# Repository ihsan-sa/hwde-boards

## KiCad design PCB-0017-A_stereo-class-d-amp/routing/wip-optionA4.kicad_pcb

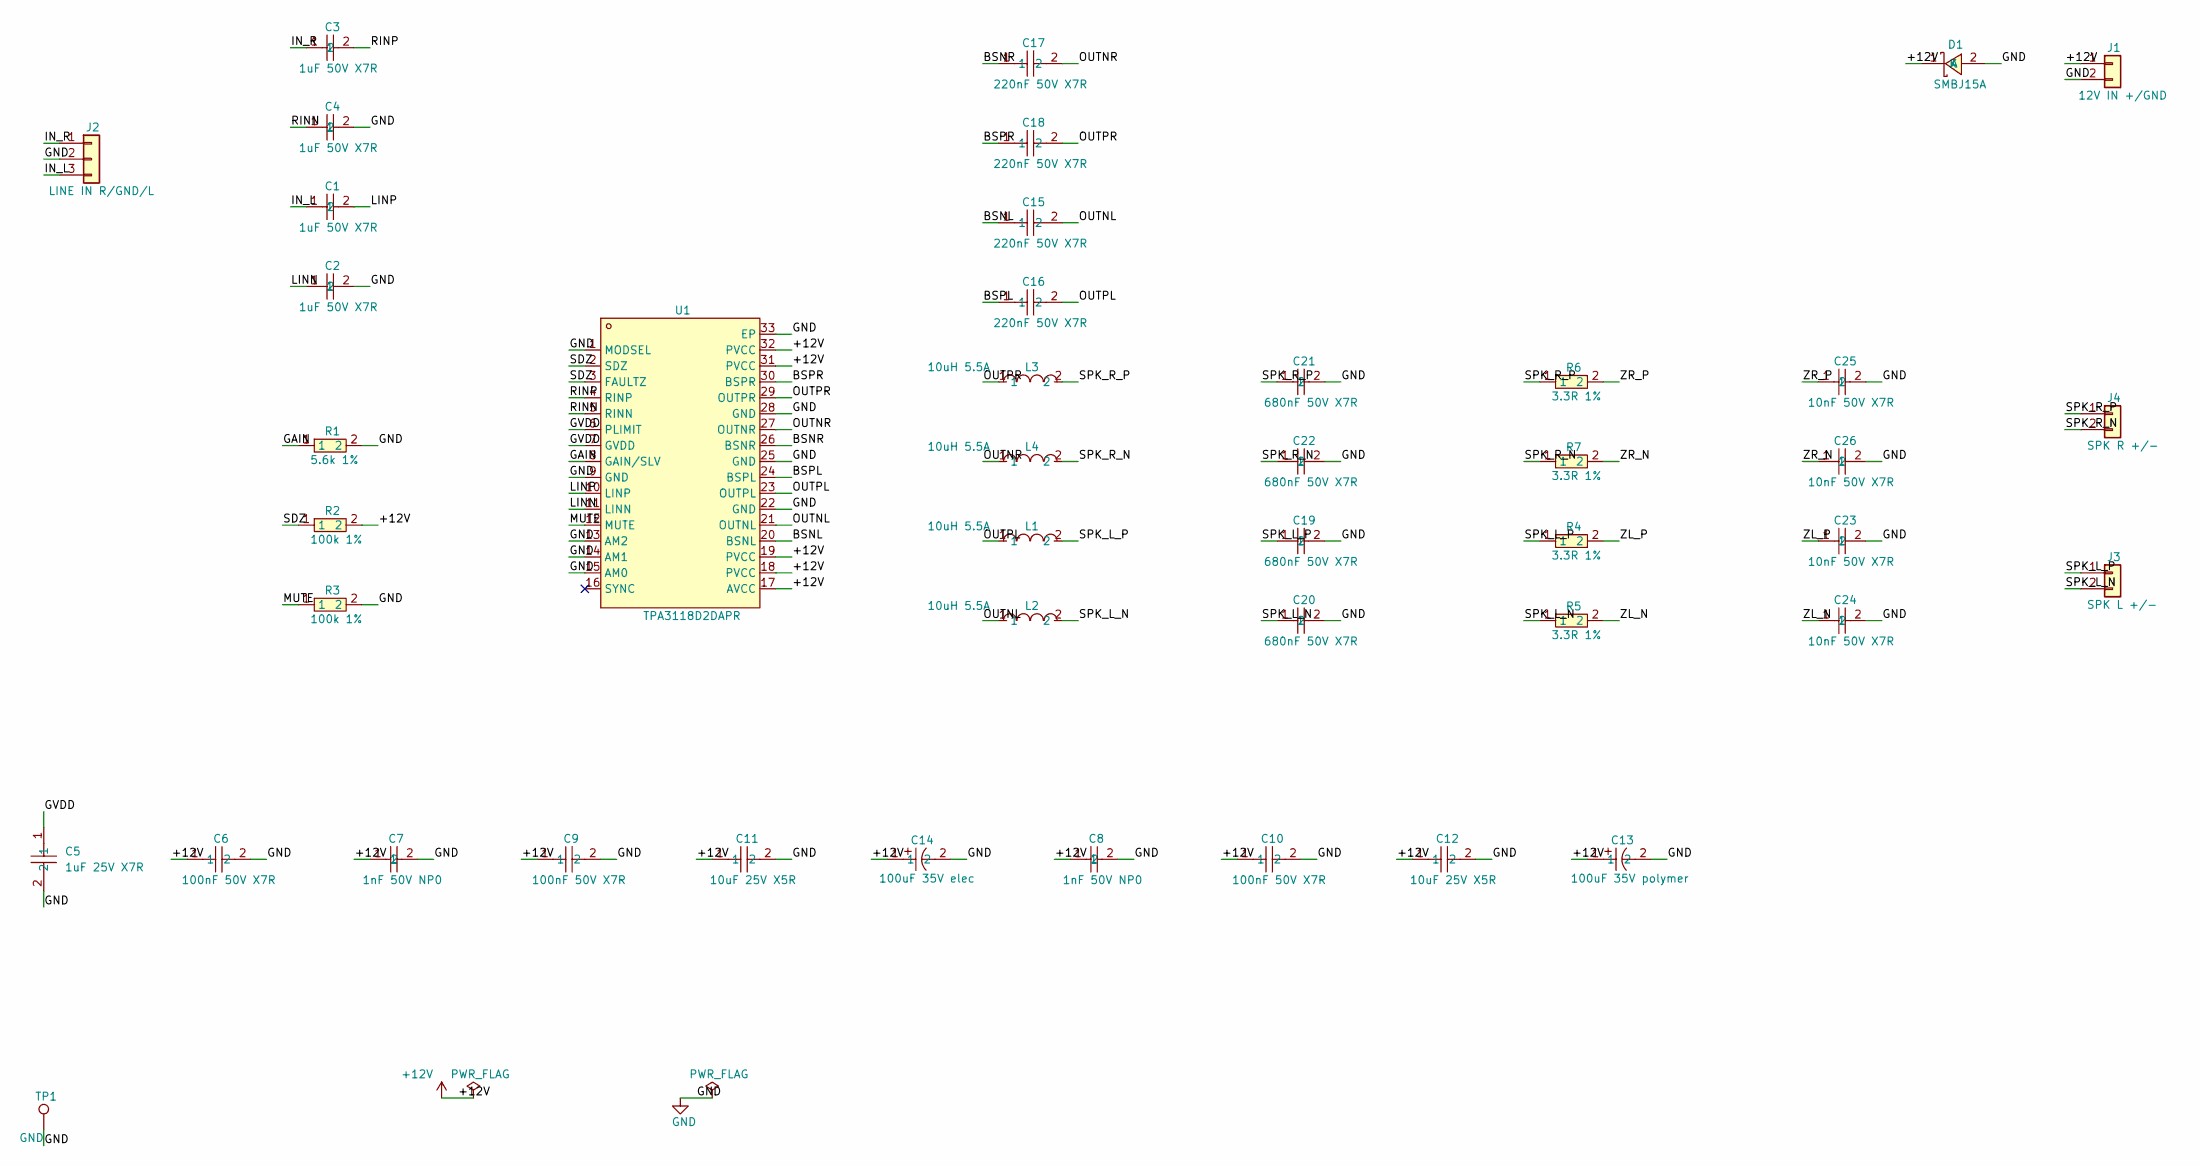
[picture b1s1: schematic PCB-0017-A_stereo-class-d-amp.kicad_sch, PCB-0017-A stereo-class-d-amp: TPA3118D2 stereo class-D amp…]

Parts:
C1, C2, C3, C4: 1uF 50V X7R; C0805; LCSC C28323
C5: 1uF 25V X7R; C0603; LCSC C106858
C6, C9, C10: 100nF 50V X7R; C0603; LCSC C14663
C7, C8: 1nF 50V NP0; C0603; LCSC C106246
C11, C12: 10uF 25V X5R; C0805; LCSC C15850
C13: 100uF 35V polymer; CAP-SMD_BD6.3-L6.6-W6.6-RD; LCSC C46550467
C14: 100uF 35V elec; CAP-SMD_BD6.3-L6.6-W6.6-LS7.3-FD; LCSC C2992596
C15, C16, C17, C18: 220nF 50V X7R; C0805; LCSC C5378
C19, C20, C21, C22: 680nF 50V X7R; C0805; LCSC C107133
C23, C24, C25, C26: 10nF 50V X7R; C0402; LCSC C15195
D1: SMBJ15A; SMB_L4.6-W3.6-LS5.3-RD; LCSC C113988
J1: 12V IN +/GND; WirePad_2P_3.0x6.0mm_P4.6mm
J2: LINE IN R/GND/L; WirePad_3P_1.5x3.0mm_P2.7mm
J3: SPK L +/-; WirePad_2P_3.0x6.0mm_P4.6mm
J4: SPK R +/-; WirePad_2P_3.0x6.0mm_P4.6mm
L1, L2, L3, L4: 10uH 5.5A; IND-SMD_L7.3-W6.6_MHCI06030; LCSC C207842
R1: 5.6k 1%; R0603; LCSC C23189
R2, R3: 100k 1%; R0603; LCSC C25803
R4, R5, R6, R7: 3.3R 1%; R0603; LCSC C137725
TP1: GND; TestPoint_SMD_1.5mm_Round
U1: TPA3118D2DAPR; HTSSOP-32_L11.0-W6.1-P0.65-LS8.1-BL-EP; LCSC C46497

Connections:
+12V: C6.1, C7.1, C8.1, C9.1, C10.1, C11.1, C12.1, C13.1, C14.1, D1.1 (K), J1.1, R2.2, U1.17 (AVCC), U1.18 (PVCC), U1.19 (PVCC), U1.31 (PVCC), U1.32 (PVCC)
/BSNL: C15.1, U1.20 (BSNL)
/BSNR: C17.1, U1.26 (BSNR)
/BSPL: C16.1, U1.24 (BSPL)
/BSPR: C18.1, U1.30 (BSPR)
/GAIN: R1.1, U1.8 (GAIN/SLV)
/GVDD: C5.1, U1.6 (PLIMIT), U1.7 (GVDD)
/IN_L: C1.1, J2.3
/IN_R: C3.1, J2.1
/LINN: C2.1, U1.11 (LINN)
/LINP: C1.2, U1.10 (LINP)
/MUTE: R3.1, U1.12 (MUTE)
/OUTNL: C15.2, L2.1, U1.21 (OUTNL)
/OUTNR: C17.2, L4.1, U1.27 (OUTNR)
/OUTPL: C16.2, L1.1, U1.23 (OUTPL)
/OUTPR: C18.2, L3.1, U1.29 (OUTPR)
/RINN: C4.1, U1.5 (RINN)
/RINP: C3.2, U1.4 (RINP)
/SDZ: R2.1, U1.2 (SDZ), U1.3 (FAULTZ)
/SPK_L_N: C20.1, J3.2, L2.2, R5.1
/SPK_L_P: C19.1, J3.1, L1.2, R4.1
/SPK_R_N: C22.1, J4.2, L4.2, R7.1
/SPK_R_P: C21.1, J4.1, L3.2, R6.1
/ZL_N: C24.1, R5.2
/ZL_P: C23.1, R4.2
/ZR_N: C26.1, R7.2
/ZR_P: C25.1, R6.2
GND: C2.2, C4.2, C5.2, C6.2, C7.2, C8.2, C9.2, C10.2, C11.2, C12.2, C13.2, C14.2, C19.2, C20.2, C21.2, C22.2, C23.2, C24.2, C25.2, C26.2, D1.2 (A), J1.2, J2.2, R1.2, R3.2, TP1.1, U1.1 (MODSEL), U1.9 (GND), U1.13 (AM2), U1.14 (AM1), U1.15 (AM0), U1.22 (GND), U1.25 (GND), U1.28 (GND), U1.33 (EP)

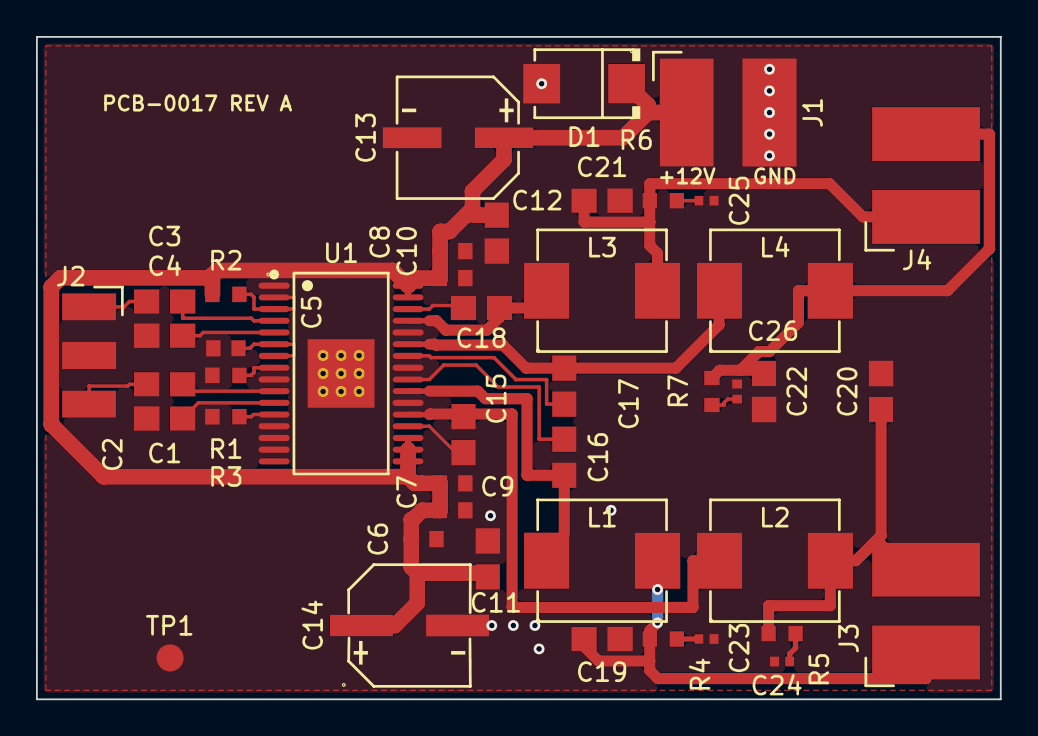
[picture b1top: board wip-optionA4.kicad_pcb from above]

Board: 2 copper layers, 53.5 x 36.8 mm, 44 parts (0 on the bottom side), 28 nets.

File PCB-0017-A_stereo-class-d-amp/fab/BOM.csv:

Comment,Designator,Footprint,LCSC Part #
1uF 50V X7R,"C1,C2,C3,C4",C0805,C28323
1uF 25V X7R,C5,C0603,C106858
100nF 50V X7R,"C6,C9,C10",C0603,C14663
1nF 50V NP0,"C7,C8",C0603,C106246
10uF 25V X5R,"C11,C12",C0805,C15850
100uF 35V polymer,C13,CAP-SMD_BD6.3-L6.6-W6.6-RD,C46550467
100uF 35V elec,C14,CAP-SMD_BD6.3-L6.6-W6.6-LS7.3-FD,C2992596
220nF 50V X7R,"C15,C16,C17,C18",C0805,C5378
680nF 50V X7R,"C19,C20,C21,C22",C0805,C107133
10nF 50V X7R,"C23,C24,C25,C26",C0402,C15195
SMBJ15A,D1,SMB_L4.6-W3.6-LS5.3-RD,C113988
10uH 5.5A,"L1,L2,L3,L4",IND-SMD_L7.3-W6.6_MHCI06030,C207842
5.6k 1%,R1,R0603,C23189
100k 1%,"R2,R3",R0603,C25803
3.3R 1%,"R4,R5,R6,R7",R0603,C137725
TPA3118D2DAPR,U1,HTSSOP-32_L11.0-W6.1-P0.65-LS8.1-BL-EP,C46497

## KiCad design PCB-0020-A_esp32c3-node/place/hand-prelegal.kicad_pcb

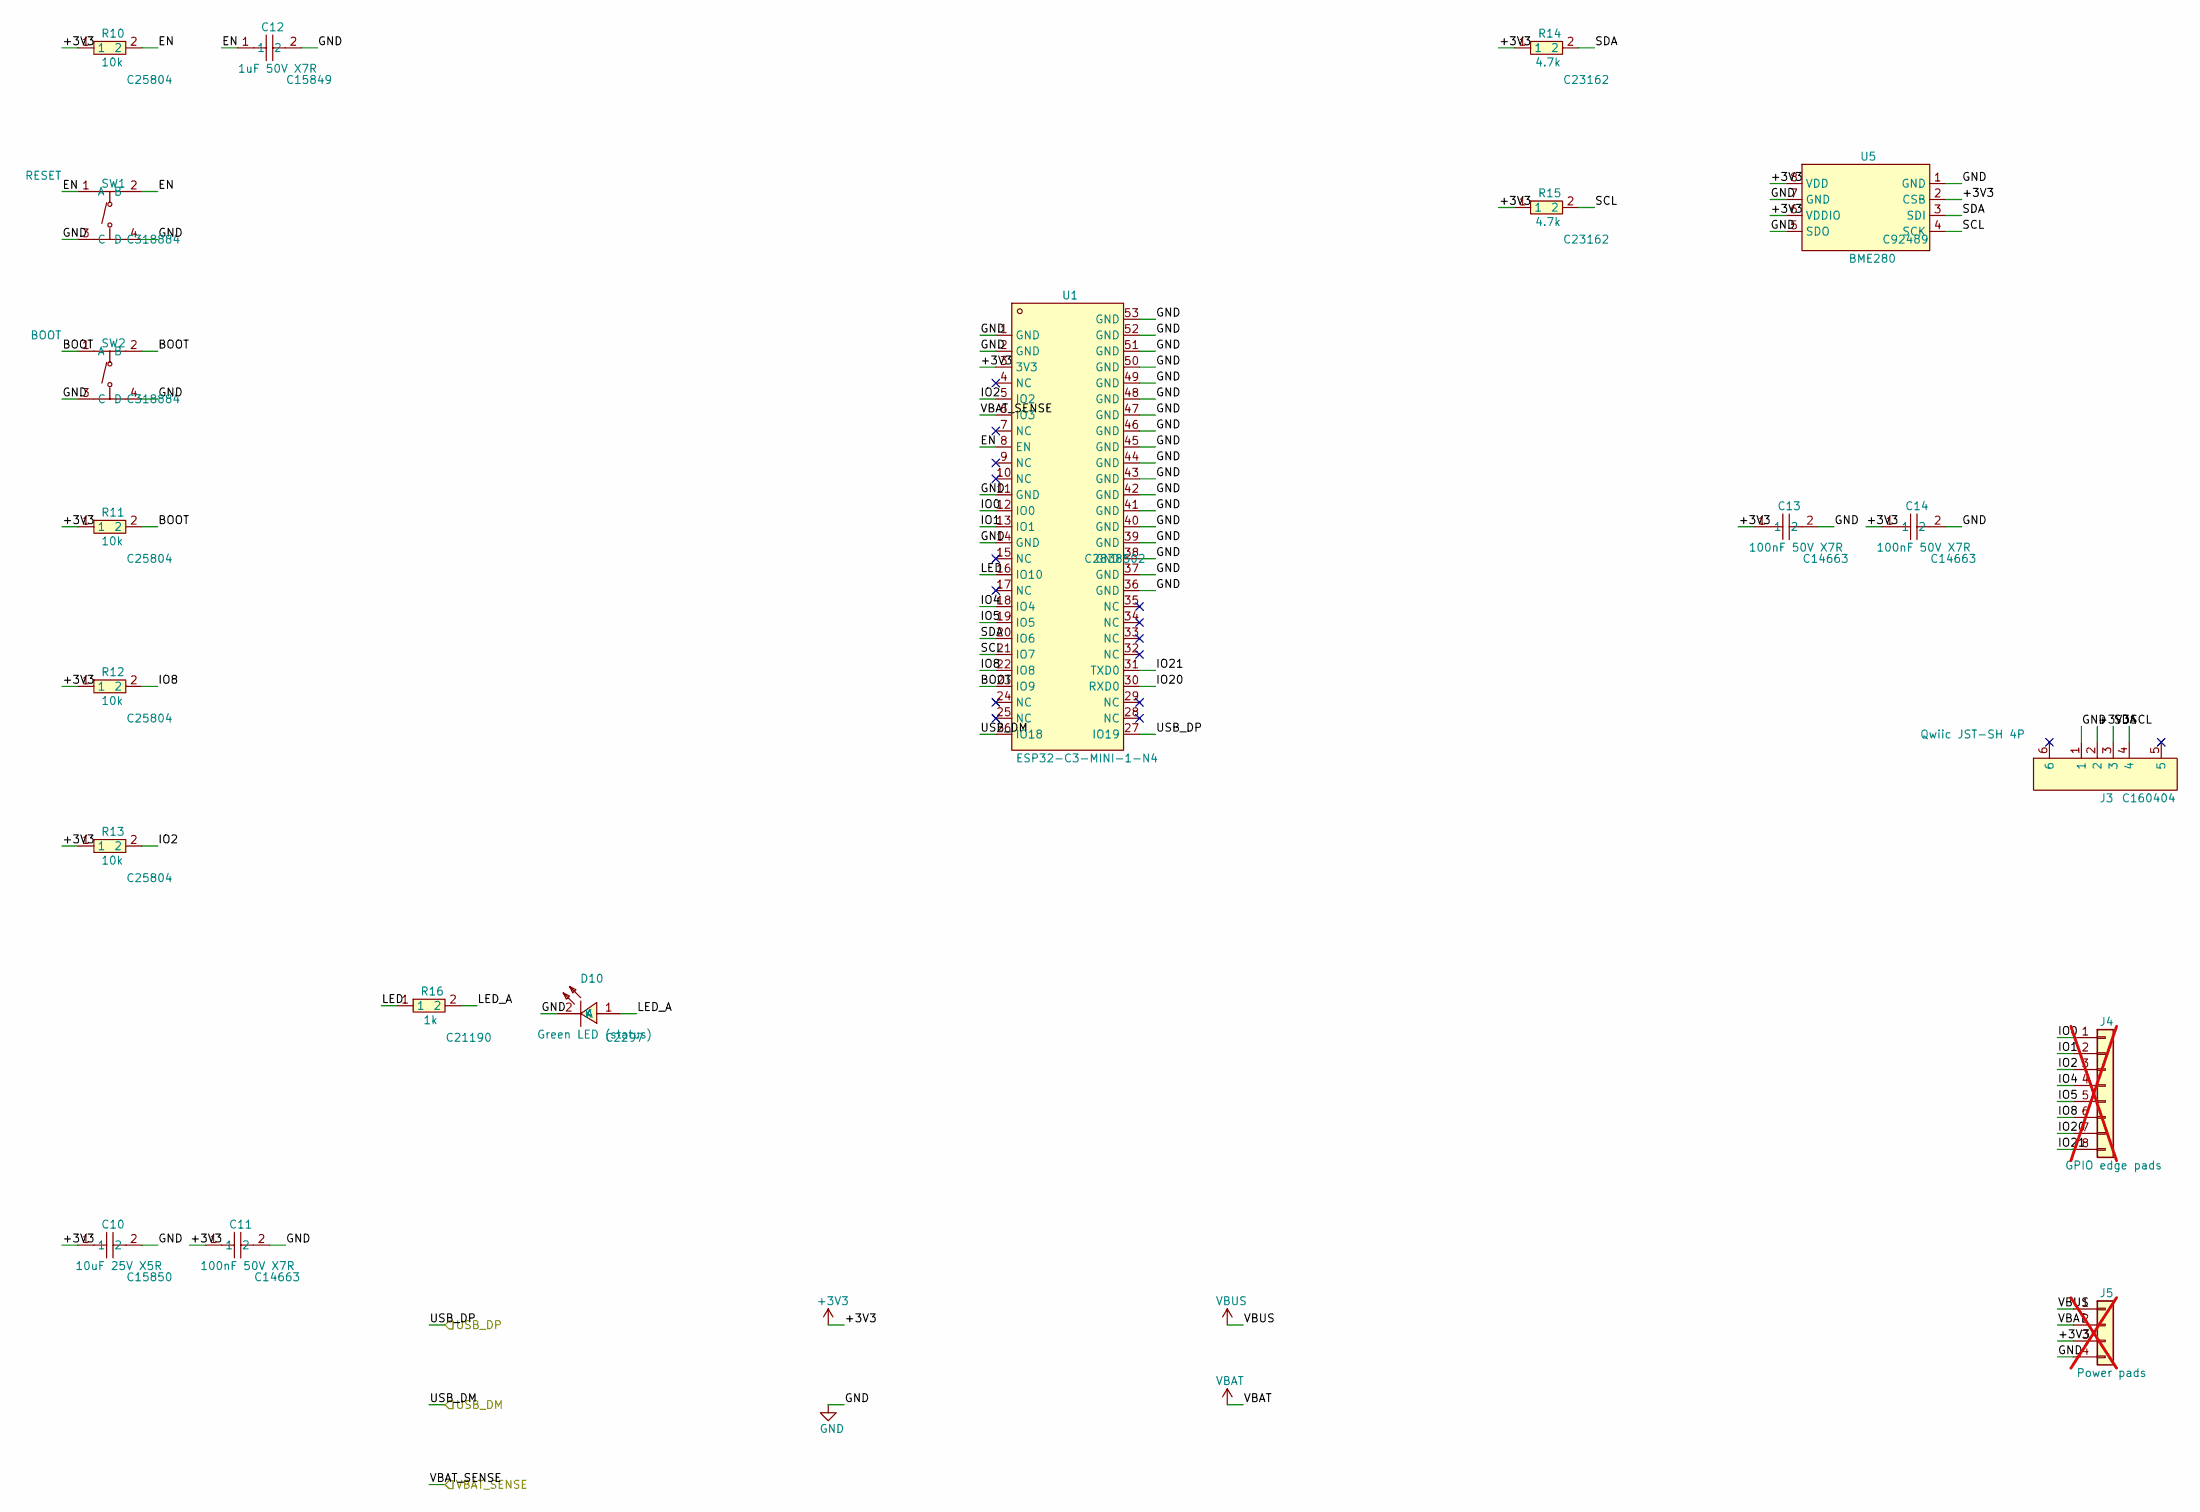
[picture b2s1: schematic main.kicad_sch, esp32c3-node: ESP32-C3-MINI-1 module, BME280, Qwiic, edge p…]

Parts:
C10: 10uF 25V X5R; C0805; LCSC C15850
C11, C13, C14: 100nF 50V X7R; C0603; LCSC C14663
C12: 1uF 50V X7R; C0603; LCSC C15849
D10: Green LED (status); LED0805-R-RD; LCSC C2297
J3: Qwiic JST-SH 4P; CONN-SMD_4P-P1.00_SM04B-SRSS-TB-LF-SN; LCSC C160404
J4: GPIO edge pads; PinHeader_1x08_P2.54mm_Vertical; not fitted
J5: Power pads; PinHeader_1x04_P2.54mm_Vertical; not fitted
R10, R11, R12, R13: 10k; R0603; LCSC C25804
R14, R15: 4.7k; R0603; LCSC C23162
R16: 1k; R0603; LCSC C21190
SW1: RESET; SW-SMD_4P-L5.1-W5.1-P3.70-LS6.5-TL_H1.5; LCSC C318884
SW2: BOOT; SW-SMD_4P-L5.1-W5.1-P3.70-LS6.5-TL_H1.5; LCSC C318884
U1: ESP32-C3-MINI-1-N4; WIFIM-SMD_ESP32-C3-MINI-1; LCSC C2838502
U5: BME280; LGA-8_BME280_BL; LCSC C92489

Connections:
+3V3: C10.1, C11.1, C13.1, C14.1, J3.2, J5.3, R10.1, R11.1, R12.1, R13.1, R14.1, R15.1, U1.3 (3V3), U5.2 (CSB), U5.6 (VDDIO), U5.8 (VDD); also elsewhere on the board
/USB_DM: U1.26 (IO18); also elsewhere on the board
/USB_DP: U1.27 (IO19); also elsewhere on the board
/VBAT_SENSE: U1.6 (IO3); also elsewhere on the board
/main/BOOT: R11.2, SW2.1 (A), SW2.2 (B), U1.23 (IO9)
/main/EN: C12.1, R10.2, SW1.1 (A), SW1.2 (B), U1.8 (EN)
/main/IO0: J4.1, U1.12 (IO0)
/main/IO1: J4.2, U1.13 (IO1)
/main/IO2: J4.3, R13.2, U1.5 (IO2)
/main/IO4: J4.4, U1.18 (IO4)
/main/IO5: J4.5, U1.19 (IO5)
/main/IO8: J4.6, R12.2, U1.22 (IO8)
/main/IO20: J4.7, U1.30 (RXD0)
/main/IO21: J4.8, U1.31 (TXD0)
/main/LED: R16.1, U1.16 (IO10)
/main/LED_A: D10.1 (A), R16.2
/main/SCL: J3.4, R15.2, U1.21 (IO7), U5.4 (SCK)
/main/SDA: J3.3, R14.2, U1.20 (IO6), U5.3 (SDI)
GND: C10.2, C11.2, C12.2, C13.2, C14.2, D10.2 (K), J3.1, J5.4, SW1.3 (C), SW1.4 (D), SW2.3 (C), SW2.4 (D), U1.1 (GND), U1.2 (GND), U1.11 (GND), U1.14 (GND), U1.36 (GND), U1.37 (GND), U1.38 (GND), U1.39 (GND), U1.40 (GND), U1.41 (GND), U1.42 (GND), U1.43 (GND), U1.44 (GND), U1.45 (GND), U1.46 (GND), U1.47 (GND), U1.48 (GND), U1.49 (GND), U1.50 (GND), U1.51 (GND), U1.52 (GND), U1.53 (GND), U5.1 (GND), U5.5 (SDO), U5.7 (GND); also elsewhere on the board
VBAT: J5.2; also elsewhere on the board
VBUS: J5.1; also elsewhere on the board

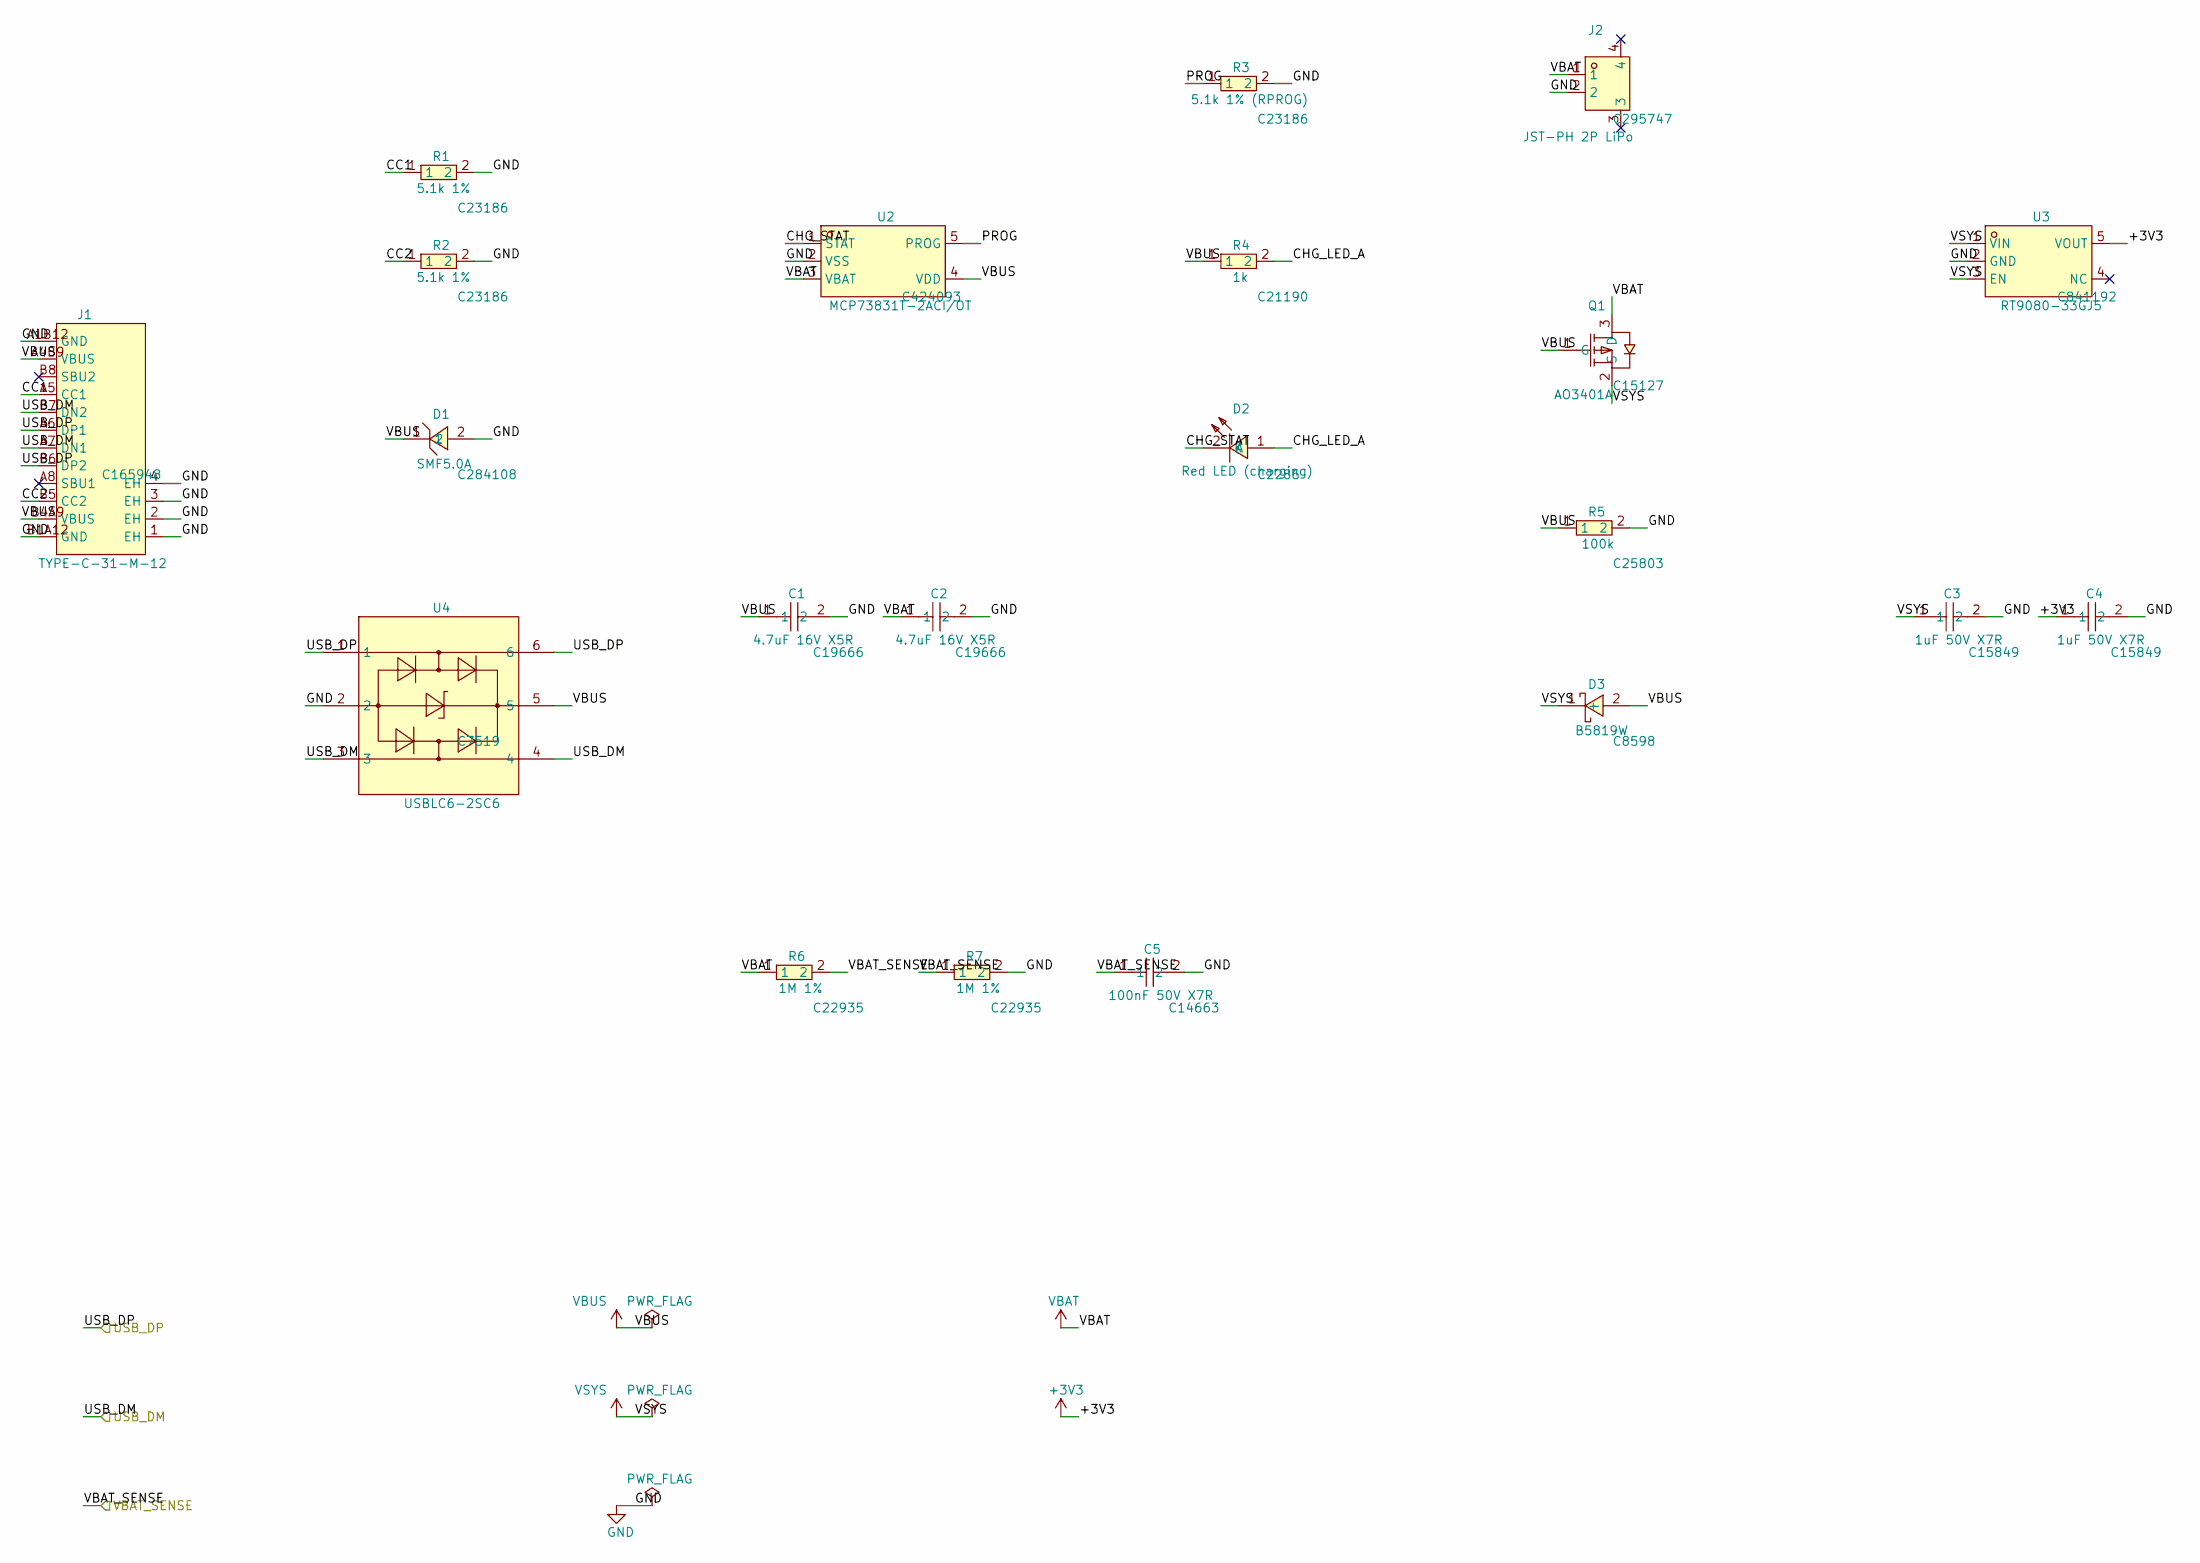
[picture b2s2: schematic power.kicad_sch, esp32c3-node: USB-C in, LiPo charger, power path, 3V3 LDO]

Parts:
C1, C2: 4.7uF 16V X5R; C0603; LCSC C19666
C3, C4: 1uF 50V X7R; C0603; LCSC C15849
C5: 100nF 50V X7R; C0603; LCSC C14663
D1: SMF5.0A; SOD-123_L2.8-W1.8-LS3.7-RD; LCSC C284108
D2: Red LED (charging); LED-SMD_L1.6-W0.8-R-RD; LCSC C2286
D3: B5819W; SOD-123_L2.7-W1.6-LS3.7-RD-1; LCSC C8598
J1: TYPE-C-31-M-12; USB-C_SMD-TYPE-C-31-M-12_1; LCSC C165948
J2: JST-PH 2P LiPo; CONN-SMD_P2.00_S2B-PH-SM4-TB-LF-SN; LCSC C295747
Q1: AO3401A; SOT-23_L2.9-W1.3-P1.90-LS2.4-BR; LCSC C15127
R1, R2: 5.1k 1%; R0603; LCSC C23186
R3: 5.1k 1% (RPROG); R0603; LCSC C23186
R4: 1k; R0603; LCSC C21190
R5: 100k; R0603; LCSC C25803
R6, R7: 1M 1%; R0603; LCSC C22935
U2: MCP73831T-2ACI/OT; SOT-23-5_L3.0-W1.7-P0.95-LS2.8-BL; LCSC C424093
U3: RT9080-33GJ5; TSOT-23-5_L2.9-W1.6-P0.95-LS2.8-BL; LCSC C841192
U4: USBLC6-2SC6; SOT-23-6_L2.9-W1.6-P0.95-LS2.8-BL; LCSC C7519

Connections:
+3V3: C4.1, U3.5 (VOUT); also elsewhere on the board
/USB_DM: J1.A7 (DN1), J1.B7 (DN2), U4.3, U4.4; also elsewhere on the board
/USB_DP: J1.A6 (DP1), J1.B6 (DP2), U4.1, U4.6; also elsewhere on the board
/VBAT_SENSE: C5.1, R6.2, R7.1; also elsewhere on the board
/power/CC1: J1.A5 (CC1), R1.1
/power/CC2: J1.B5 (CC2), R2.1
/power/CHG_LED_A: D2.1 (A), R4.2
/power/CHG_STAT: D2.2 (K), U2.1 (STAT)
/power/PROG: R3.1, U2.5 (PROG)
GND: C1.2, C2.2, C3.2, C4.2, C5.2, D1.2, J1.1 (EH), J1.2 (EH), J1.3 (EH), J1.4 (EH), J1.A1B12 (GND), J1.B1A12 (GND), J2.2, R1.2, R2.2, R3.2, R5.2, R7.2, U2.2 (VSS), U3.2 (GND), U4.2; also elsewhere on the board
VBAT: C2.1, J2.1, Q1.3 (D), R6.1, U2.3 (VBAT); also elsewhere on the board
VBUS: C1.1, D1.1, D3.2 (+), J1.A4B9 (VBUS), J1.B4A9 (VBUS), Q1.1 (G), R4.1, R5.1, U2.4 (VDD), U4.5; also elsewhere on the board
VSYS: C3.1, D3.1 (-), Q1.2 (S), U3.1 (VIN), U3.3 (EN)

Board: 2 copper layers, 41 parts (0 on the bottom side), 27 nets, no tracks yet.

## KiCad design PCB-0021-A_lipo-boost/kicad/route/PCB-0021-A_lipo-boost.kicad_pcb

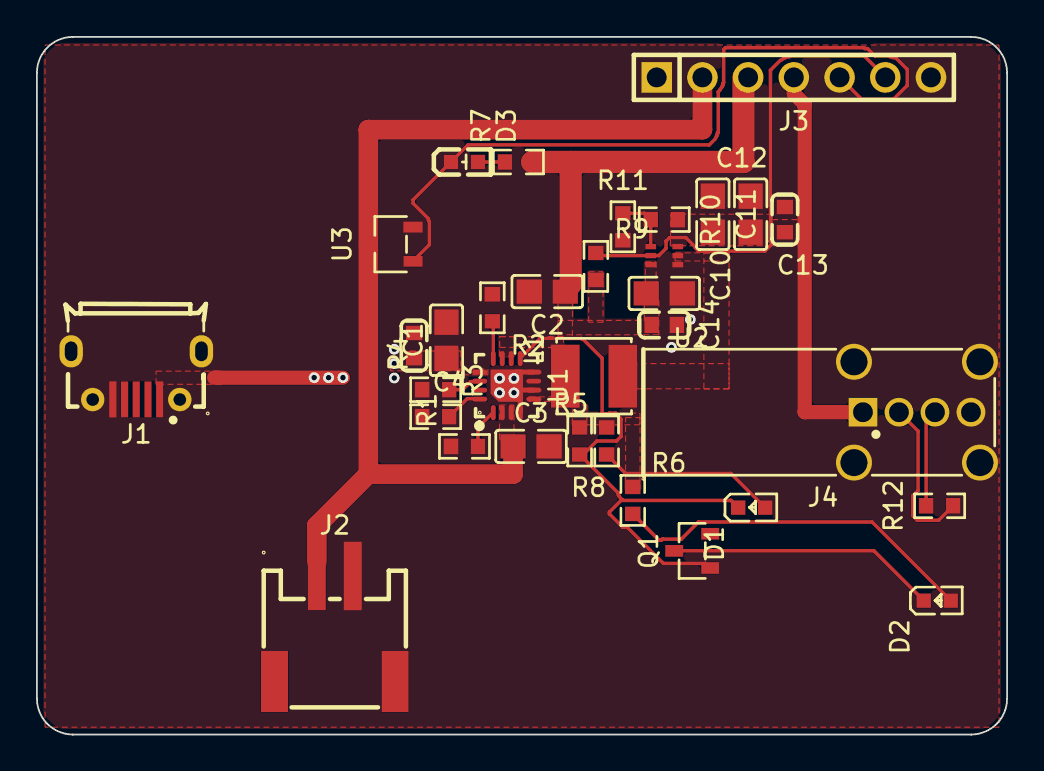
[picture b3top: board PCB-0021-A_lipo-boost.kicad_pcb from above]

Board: 2 copper layers, 53.9 x 38.8 mm, 33 parts (0 on the bottom side), 21 nets.

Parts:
C1: 4.7uF 25V X5R; C0805
C2, C3, C10: 10uF 25V X5R; C0805
C4, C13, C14: 100nF 50V X7R; C0603
C11, C12: 22uF 25V X5R; C0805
D1: ORH-R36A orange; LED0603-RD
D2: KT-0603G green; LED0603-RD
D3: KT-0603R red; LED-SMD_L1.6-W0.8-R-RD
J1: MicroXNJ; MICRO-USB-SMD_MICROXNJ_1
J2: S2B-PH-SM4-TB(LF)(SN); CONN-SMD_P2.00_S2B-PH-SM4-TB-LF-SN
J3: HX PZ2.54-1x7P; HDR-TH_7P-P2.54-V-M
J4: Type-A-AF90; USB-A-TH_U-A-24DD-Y-13
L1: 1uH; IND-SMD_L4.0-W4.0
Q1: 2N7002; SOT-23-3_L2.9-W1.3-P1.90-LS2.4-BR
R1: 10k; R0603
R2: 1.2k; R0603
R3, R5, R7: 1k; R0603
R4: 51k; R0603
R6: 470R; R0603
R8, R9, R11: 100k; R0603
R10: 732k; R0603
R12: 0R; R0603
U1: BQ24074RGTR; QFN-16_L3.0-W3.0-P0.50-TL-EP1.7
U2: TPS61023DRLR; SOT-563_L1.6-W1.2-P0.50-LS1.6-BR
U3: MSXC61CN3302MR; SOT-23-3_L2.9-W1.6-P1.90-LS2.8-BR

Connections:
+5V: C11.1, C12.1, C13.1, J3.4, J4.1, R10.1, U2.6
+SYS: C2.1, C10.1, C14.1, J3.3, L1.1, R5.1, R6.1, R7.1, R8.1, R9.1, U1.5, U1.10, U1.11, U2.3
/CHG: D1.1, Q1.1, R8.2, U1.9
/CHG_A: D1.2, R5.2
/DONE_A: D2.2, R6.2
/DONE_K: D2.1, Q1.3
/EN: J3.6, R9.2, U2.2
/FB: R10.2, R11.1, U2.1
/ILIM: R2.1, U1.12
/ISET: R3.1, U1.16
/LBO: D3.2, J3.5, U3.1
/LB_A: D3.1, R7.2
/PGOOD: Q1.2, U1.7
/SW: L1.2, U2.5
/TMR: R4.1, U1.14
/TS: R1.1, U1.1
/USB_DM: J4.2, R12.2
/USB_DP: J4.3, R12.1
GND: C1.2, C2.2, C3.2, C4.2, C10.2, C11.2, C12.2, C13.2, C14.2, J1.5, J1.6, J1.7, J1.8, J1.9, J2.2, J3.1, J3.7, J4.4, J4.5, J4.6, R1.2, R2.2, R3.2, R4.2, R11.2, U1.4, U1.6, U1.8, U1.17, U2.4, U3.2
VBAT: C3.1, J2.1, J3.2, U1.2, U1.3, U3.3
VBUS: C1.1, C4.1, J1.1, U1.13
